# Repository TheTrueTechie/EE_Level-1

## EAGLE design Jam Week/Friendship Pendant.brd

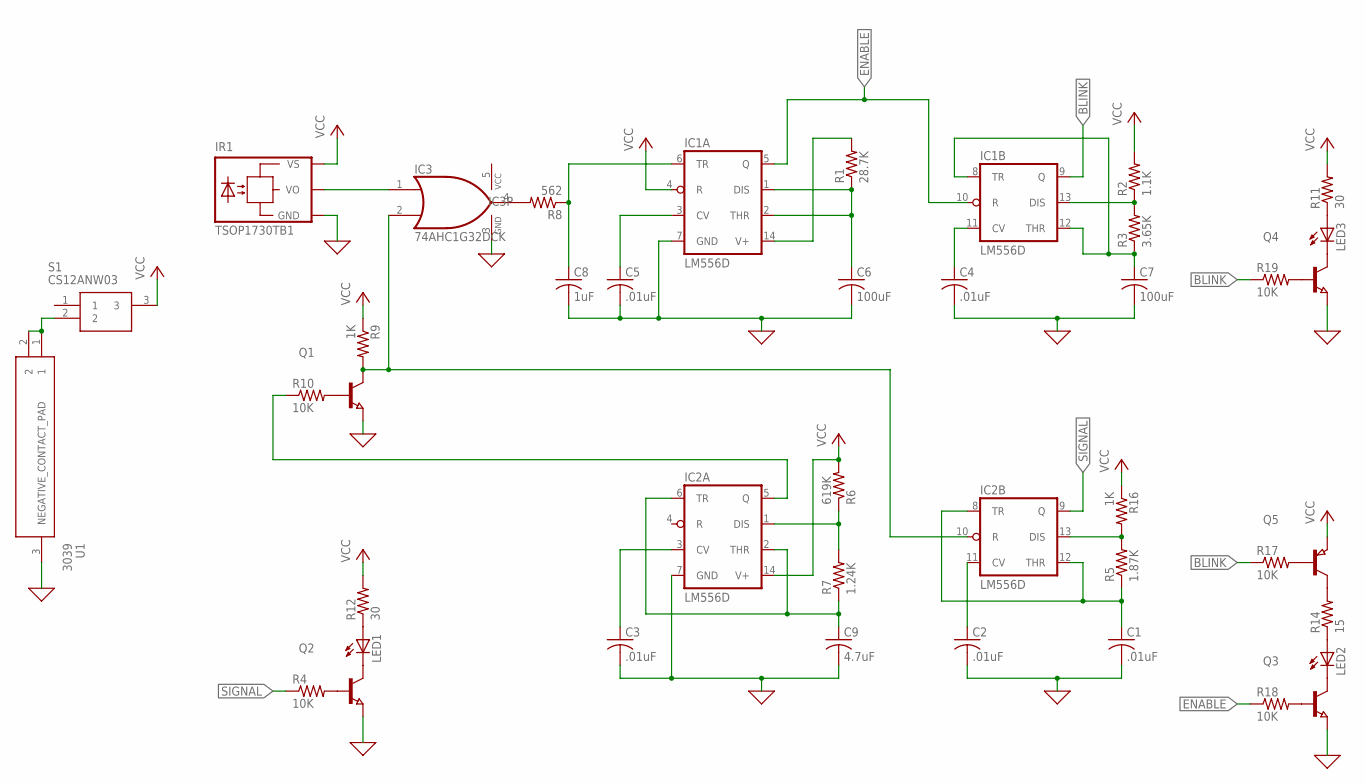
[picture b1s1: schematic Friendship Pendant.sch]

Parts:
C1: .01uF; C0805; MOUSER# 603-CC0805JRX7R9BB103
C2, C3, C4, C5: .01uF; C0805; MOUSER# 603-CC0805KRX7R9BB103
C6, C7: 100uF; C0805; MOUSER# 81-GRM31CR60J107KE39L
C8: 1uF; C0805; MOUSER# 80-C0805C105K3R
C9: 4.7uF; C0805; MOUSER# 791-0805X475M250CT
IC1, IC2: LM556D; SO14; MOUSER# 511-TS556IDTTR
IC3: 74AHC1G32DCK; SC70-5; MOUSER# 595-SN74AUP1G32DCKR
IR1: TSOP1730TB1; TSOP17_TB1; MOUSER# 78-TSOP31330
LED1: LEDIRL80A; IRL80A; MOUSER# 782-TSAL6200
LED2: LED5MM; MOUSER# 859-LTL-307GLC
LED3: LED5MM; MOUSER# 645-521-9672F
Q1, Q2, Q3, Q4: NPN-TRANSISTOR_SOT23; SOT23; MOUSER# 726-BCW66KHE6327HTSA1
Q5: PNP-TRANSISTOR_SOT23; SOT23; MOUSER# 583-BC856A-T
R1: 28.7K; R0805; MOUSER# 652-CR0805-FX-2872ELF
R2: 1.1K; R0805; MOUSER# 652-CR0805-FX-1101ELF
R3: 3.65K; R0805; MOUSER# 652-CR0805-FX-3651ELF
R4, R10, R17, R18, R19: 10K; R0805; MOUSER# 652-CR0805-FX-1002ELF
R5: 1.87K; R0805; MOUSER# 652-CR0805-FX-1871ELF
R6: 619K; R0805; MOUSER# 652-CR0805-FX-6193ELF
R7: 1.24K; R0805; MOUSER# 652-CR0805-FX-1241ELF
R8: 562; R0805; MOUSER# 652-CR0805-FX-5620ELF
R9, R16: 1K; R0805; MOUSER# 652-CR0805-FX-1001ELF
R11, R12: 30; R0805; MOUSER# 652-CR0805-JW-300ELF
R14: 15; R0805; MOUSER# 652-CR0805-FX-15R0ELF
S1: CS12ANW03
U1: 3039; MOUSER# 534-3039

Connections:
BLINK: IC1.9 (Q), R17.1, R19.1
ENABLE: IC1.5 (Q), IC1.10 (R), R18.1
unnamed: IC1.13 (DIS), R2.1, R3.2
unnamed: IC2.1 (DIS), R6.1, R7.2
unnamed: IC3.4 (O), R8.2
unnamed: IC2.10 (R), IC3.2 (I1), Q1.3 (C), R9.2
unnamed: LED1.A, R12.1
unnamed: Q3.1 (B), R18.2
unnamed: Q4.1 (B), R19.2
unnamed: Q5.1 (B), R17.2
unnamed: LED1.K (C), Q2.3 (C)
unnamed: Q2.1 (B), R4.2
unnamed: IC3.1 (I0), IR1.VO
unnamed: Q1.1 (B), R10.2
unnamed: IC2.5 (Q), R10.1
unnamed: C3.1, IC2.3 (CV)
unnamed: S1.2, U1.1, U1.2
unnamed: C9.1, IC2.2 (THR), IC2.6 (TR), R7.1
unnamed: C8.1, IC1.6 (TR), R8.1
unnamed: C5.1, IC1.3 (CV)
unnamed: C6.1, IC1.1 (DIS), IC1.2 (THR), R1.1
unnamed: IC1.14 (V+), R1.2
unnamed: C4.1, IC1.11 (CV)
unnamed: C7.1, IC1.8 (TR), IC1.12 (THR), R3.1
unnamed: LED3.A, R11.1
unnamed: LED3.K (C), Q4.3 (C)
unnamed: Q5.3 (C), R14.2
unnamed: LED2.A, R14.1
unnamed: LED2.K (C), Q3.3 (C)
unnamed: C2.1, IC2.11 (CV)
unnamed: C1.1, IC2.8 (TR), IC2.12 (THR), R5.1
unnamed: IC2.13 (DIS), R5.2, R16.2
SIGNAL: IC2.9 (Q), R4.1
VCC: IC1.4 (R), IC2.14 (V+), IC3.5 (VCC), IR1.VS, Q5.2 (E), R2.2, R6.2, R9.1, R11.2, R12.2, R16.1, S1.3

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
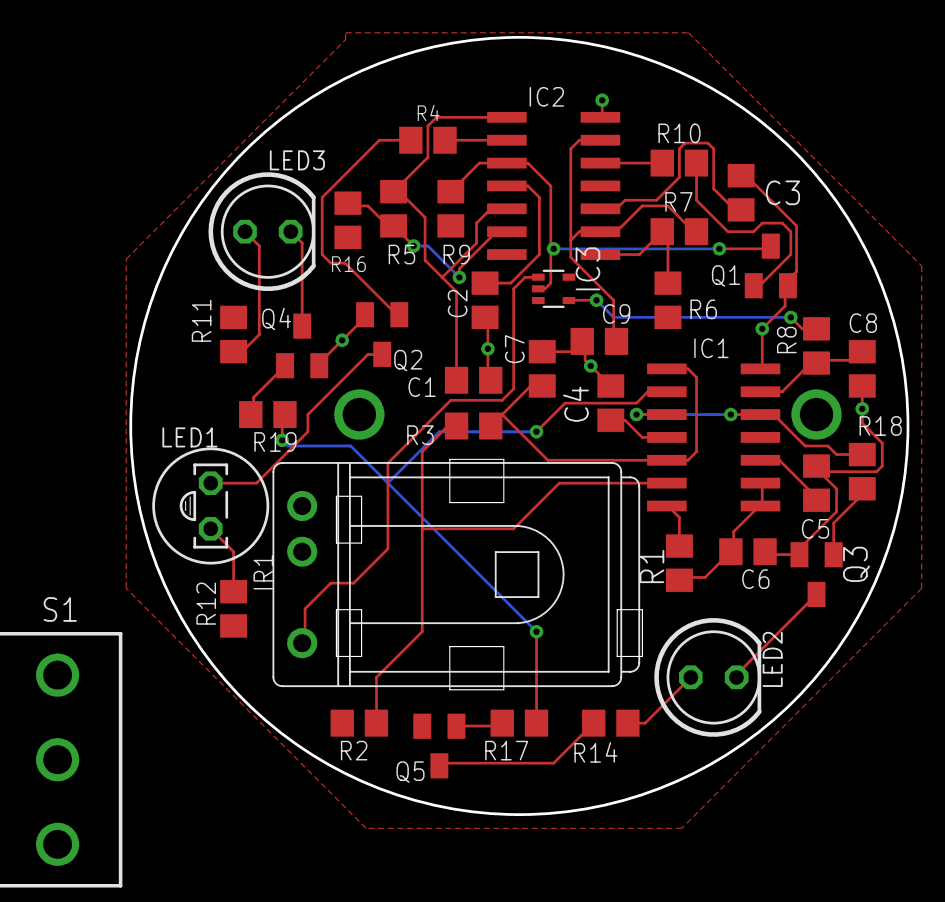
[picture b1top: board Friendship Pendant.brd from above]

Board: 2 copper layers, 43.2 x 43.2 mm, 40 parts (1 on the bottom side), 35 nets.

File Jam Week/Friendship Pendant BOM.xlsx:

Qty | Value | MOUSER# | Ordered | Device | Package | Parts | Description | MOUSER_PART_NUMBER | MOUSER_PRICE-STOCK | MPN
2 | LM556D | 511-TS556IDTTR | X | LM556D | SO14 | IC1, IC2 | Dual TIMER
1 | 3039 | 534-3039 | X | 3039 | 3039 | U1 | Coin Cell Battery Holders THM COIN CELL CLIP | 534-3039 | https://www.mouser.com/Search/Refine.aspx?Keyword=534-3039
1 |  | 583-BC856A-T | X | PNP-TRANSISTOR_SOT23 | SOT23 | Q5 | PNP TRANSISTOR
1 | 74AHC1G32DCK | 595-SN74AUP1G32DCKR | X | 74AHC1G32DCK | SC70-5 | IC3 | 2-input OR gate |  |  | SN74AUP1G32DCKR
1 | .01uF | 603-CC0805JRX7R9BB103 | X | C-USC0805 | C0805 | C1 | CAPACITOR, American symbol |  |  | CC0805JRX7R9BB103
4 | .01uF | 603-CC0805KRX7R9BB103 | X | C-USC0805 | C0805 | C2, C3, C4, C5 | CAPACITOR, American symbol |  |  | CC0805KRX7R9BB103
1 |  | 645-521-9672F |  | LED5MM | LED5MM | LED3 | LED |  |  | 521-9672F
2 | 1K | 652-CR0805-FX-1001ELF |  | R-US_R0805 | R0805 | R9, R16 | RESISTOR, American symbol |  |  | CR0805-FX-1001ELF
5 | 10K | 652-CR0805-FX-1002ELF |  | R-US_R0805 | R0805 | R4, R10, R17, R18, R19 | RESISTOR, American symbol |  |  | CR0805-FX-1002ELF
1 | 1.1K | 652-CR0805-FX-1101ELF |  | R-US_R0805 | R0805 | R2 | RESISTOR, American symbol |  |  | CR0805-FX-1101ELF
1 | 1.24K | 652-CR0805-FX-1241ELF |  | R-US_R0805 | R0805 | R7 | RESISTOR, American symbol |  |  | CR0805-FX-1241ELF
1 | 15 | 652-CR0805-FX-15R0ELF |  | R-US_R0805 | R0805 | R14 | RESISTOR, American symbol |  |  | CR0805-FX-15R0ELF
1 | 1.87K | 652-CR0805-FX-1871ELF |  | R-US_R0805 | R0805 | R5 | RESISTOR, American symbol |  |  | CR0805-FX-1871ELF
1 | 28.7K | 652-CR0805-FX-2872ELF |  | R-US_R0805 | R0805 | R1 | RESISTOR, American symbol |  |  | CR0805-FX-2872ELF
1 | 3.65K | 652-CR0805-FX-3651ELF |  | R-US_R0805 | R0805 | R3 | RESISTOR, American symbol |  |  | CR0805-FX-3651ELF
1 | 562 | 652-CR0805-FX-5620ELF |  | R-US_R0805 | R0805 | R8 | RESISTOR, American symbol |  |  | CR0805-FX-5620ELF
1 | 619K | 652-CR0805-FX-6193ELF |  | R-US_R0805 | R0805 | R6 | RESISTOR, American symbol |  |  | CR0805-FX-6193ELF
2 | 30 | 652-CR0805-JW-300ELF |  | R-US_R0805 | R0805 | R11, R12 | RESISTOR, American symbol |  |  | CR0805-JW-300ELF
4 |  | 726-BCW66KHE6327HTSA1 |  | NPN-TRANSISTOR_SOT23 | SOT23 | Q1, Q2, Q3, Q4 | NPN TRANSISTOR |  |  | BCW66KHE6327HTSA1
1 |  | 782-TSAL6200 |  | LEDIRL80A | IRL80A | LED1 | LED |  |  | TSAL6200
1 | TSOP1730TB1 | 78-TSOP31330 |  | TSOP1730TB1 | TSOP17_TB1 | IR1 | TSOP17..TB1 IR Receiver Modules for Remote Control Systems |  |  | TSOP31330
1 | 4.7uF | 791-0805X475M250CT |  | C-USC0805 | C0805 | C9 | CAPACITOR, American symbol |  |  | 0805X475M250CT
1 | 1uF | 80-C0805C105K3R |  | C-USC0805 | C0805 | C8 | CAPACITOR, American symbol |  |  | C0805C105K3R
2 | 100uF | 81-GRM31CR60J107KE39L |  | C-USC0805 | C0805 | C6, C7 | CAPACITOR, American symbol |  |  | GRM31CR60J107KE39L
1 |  | 859-LTL-307GLC |  | LED5MM | LED5MM | LED2 | LED |  |  | LTL-307GLC
1 | CS12ANW03 |  |  | CS12ANW03 | CS12ANW03 | S1 | NKK SWITCHES - CS12ANW03 - SWITCH, SLIDE, SPDT, 3A, 250V, TH | 633-CS12ANW03 | https://www.mouser.com/Search/Refine.aspx?Keyword=633-CS12ANW03

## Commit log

2018-07-21 Finished Photosensor
    Finished the Photosensor schematic, ran tests to find the values.
2018-07-21 Fixed Resistor
    Added a parameter to resistor.
2018-08-25 Completed Lesson 8
2018-09-01 Finished Lesson 9
    Finished making lesson 9 circuit.
2018-10-13 Learning Checkpoint
2019-03-30 Updating files
2019-05-04 Lesson 22
    Finished Lesson 22
2019-05-25 Lesson 22
    Last weeks update
2019-05-25 Lesson22
    Lesson22 Final Circuit, still in progress
2019-06-15 Lesson 24 Circuit
2019-06-22 Lesson 25
2019-07-06 Lesson 26
    Made Spice Circuit
2019-07-13 Passive Filters v2
    Fixed version of Passive Filters
2019-07-16 555 Timer Plan
    Finished the schematic for the first LED
2019-07-17 Transmitter part
2019-07-18 Day 4
2019-07-20 Added orGate
2019-08-17 Emitter Follower + Project
2019-08-24 Did stuff
2019-08-31 Left off with the 2nd LED voltages
2019-09-21 Done
2019-09-21 Started eagle
2019-09-28 Worked on eagle more
2019-10-05 Worked more 10/5
    guyng
2019-10-12 Added LEDs
    db
2019-10-19 Almost done with eagle scematic
2019-11-02 Working on layout
2019-11-09 Next class resolve air wire
2019-11-16 Almost done,
2019-11-16 added switch and ordered without switch
2019-11-25 Updated some parts before ordering from Mouser
2019-12-21 final day
